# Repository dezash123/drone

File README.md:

# drone
My drone: coded in rust, frame designed in [onshape](https://cad.onshape.com/documents/91c1fbb6d04f2dc72182ab9c/w/1d5775c73044c5da3d093724/e/ebeab2adf1bd9151a745482d), and PCB designed in KiCAD.

much of this was learned through trial and error, and looking back, kinda embarrassing, but I'll keep this around since it did work

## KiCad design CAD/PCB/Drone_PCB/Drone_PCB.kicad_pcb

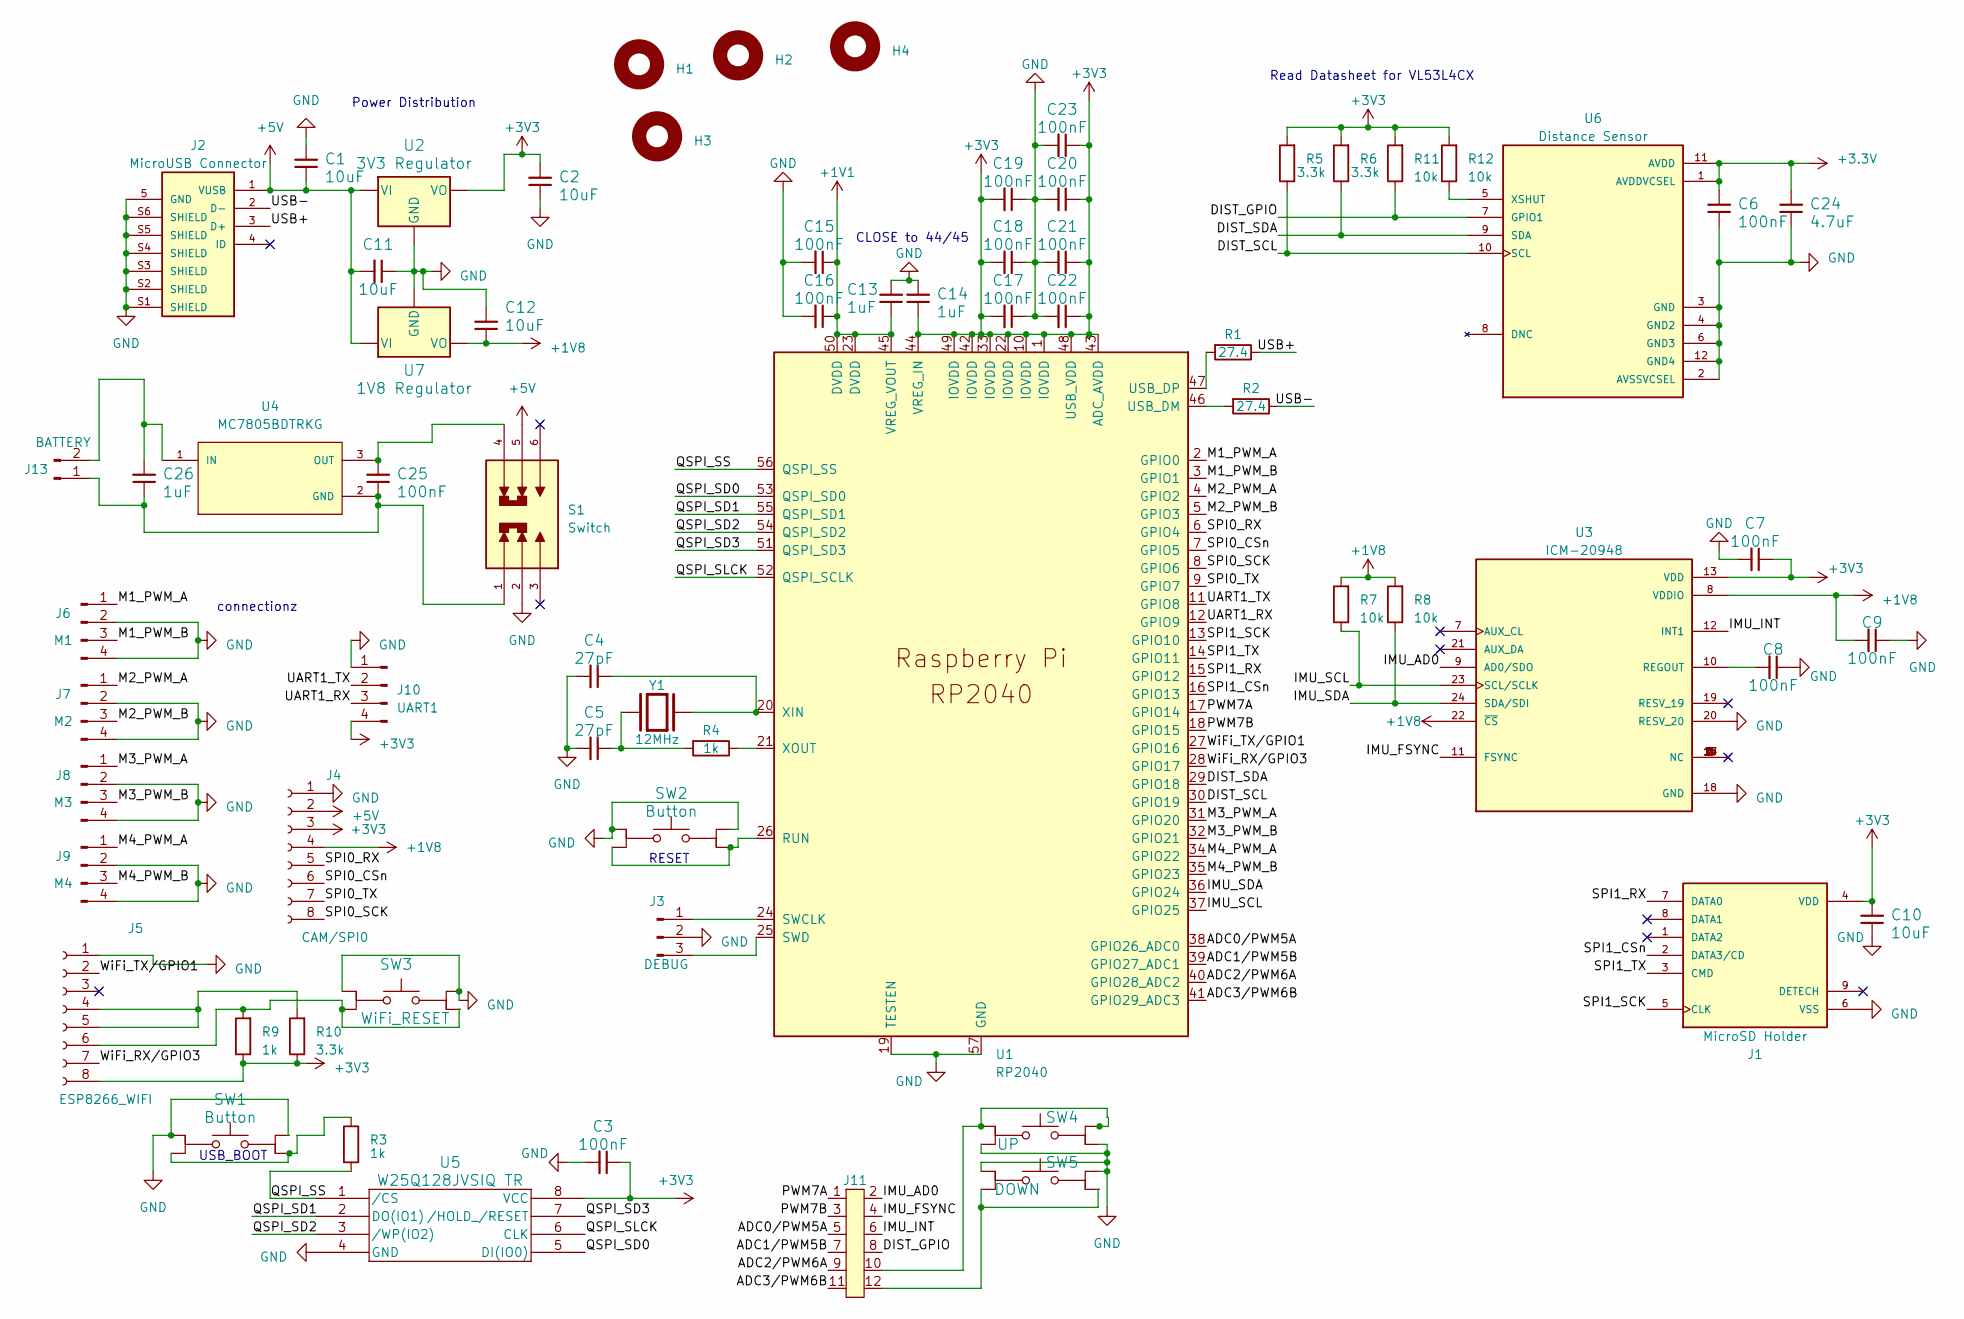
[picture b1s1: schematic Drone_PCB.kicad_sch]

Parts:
C1, C2, C10, C11, C12: 10uF; CAP_CL21_SAM
C3, C6, C7, C8, C9, C15, C16, C17, C18, C19, C20, C21, C22, C23, C25: 100nF; CAPC1005X56N
C4, C5: 27pF; CAPC1005X55N
C13, C14, C26: 1uF; CAPC1608X90N
C24: 4.7uF; CAPC1005X60N
H1, H2, H3, H4: MountingHole_2.2mm_M2
J1: MicroSD Holder; GCT_MEM2051-00-195-00-A
J2: MicroUSB Connector; AMPHENOL_10118193-0001LF; PARTREV E
J3: DEBUG; PinHeader_1x03_P2.54mm_Vertical
J4: CAM/SPI0; PinSocket_2x04_P2.54mm_Vertical
J5: ESP8266_WIFI; PinSocket_2x04_P2.54mm_Vertical
J6: M1; PinHeader_1x04_P2.54mm_Vertical
J7: M2; PinHeader_1x04_P2.54mm_Vertical
J8: M3; PinHeader_1x04_P2.54mm_Vertical
J9: M4; PinHeader_1x04_P2.54mm_Vertical
J10: UART1; PinHeader_1x04_P2.54mm_Vertical
J11: PinSocket_2x06_P2.54mm_Vertical
J13: BATTERY; AMASS_XT60-M_1x02_P7.20mm_Vertical
R1, R2: 27.4; RESC1005X35N
R3, R4, R9: 1k; RESC1005X40
R5, R6, R10: 3.3k; RESC1005X40
R7, R8, R11, R12: 10k; RESC1005X40N
S1: Switch; SW_EG2208; PARTREV C
SW1, SW2: Button; PTS 647 SN50 SMTR2 LFS
SW3: WiFi_RESET; PTS 647 SN50 SMTR2 LFS
SW4: UP; PTS 647 SN50 SMTR2 LFS
SW5: DOWN; PTS 647 SN50 SMTR2 LFS
U1: RP2040; RP2040-QFN-56
U2: 3V3 Regulator; SOT230P700X185-4N
U3: ICM-20948; QFN40P300X300X105-24N; PARTREV 1.3
U4: MC7805BDTRKG; DPAK229P990X238-4N; PARTREV 27
U5: W25Q128JVSIQ TR; SOIC_208MIL_WIN
U6: Distance Sensor; XCDR_VL53L4CXV0DH_1; PARTREV 4
U7: 1V8 Regulator; SOT223-3_ONS
Y1: 12MHz; XTAL_ABLS-12.000MHZ-K2-T; PARTREV 02.16.2021

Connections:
+1V1: C13.1, C15.1, C16.1, U1.23 (DVDD), U1.45 (VREG_VOUT), U1.50 (DVDD)
+1V8: C9.2, C12.1, J4.4, R7.2, R8.2, U3.8 (VDDIO), U3.22 (~CS), U7.2 (VO)
+5V: C1.1, C11.2, J2.1 (VUSB), J4.2, S1.5, U2.3 (VI), U7.3 (VI)
/ADC0/PWM5A: J11.5, U1.38 (GPIO26_ADC0)
/ADC1/PWM5B: J11.7, U1.39 (GPIO27_ADC1)
/ADC2/PWM6A: J11.9, U1.40 (GPIO28_ADC2)
/ADC3/PWM6B: J11.11, U1.41 (GPIO29_ADC3)
/DIST_GPIO: J11.8, R11.1, U6.7 (GPIO1)
/DIST_SCL: R5.1, U1.30 (GPIO19), U6.10 (SCL)
/DIST_SDA: R6.1, U1.29 (GPIO18), U6.9 (SDA)
/IMU_AD0: J11.2, U3.9 (AD0/SDO)
/IMU_FSYNC: J11.4, U3.11 (FSYNC)
/IMU_INT: J11.6, U3.12 (INT1)
/IMU_SCL: R7.1, U1.37 (GPIO25), U3.23 (SCL/SCLK)
/IMU_SDA: R8.1, U1.36 (GPIO24), U3.24 (SDA/SDI)
/M1_PWM_A: J6.1, U1.2 (GPIO0)
/M1_PWM_B: J6.3, U1.3 (GPIO1)
/M2_PWM_A: J7.1, U1.4 (GPIO2)
/M2_PWM_B: J7.3, U1.5 (GPIO3)
/M3_PWM_A: J8.1, U1.31 (GPIO20)
/M3_PWM_B: J8.3, U1.32 (GPIO21)
/M4_PWM_A: J9.1, U1.34 (GPIO22)
/M4_PWM_B: J9.3, U1.35 (GPIO23)
/PWM7A: J11.1, U1.17 (GPIO14)
/PWM7B: J11.3, U1.18 (GPIO15)
/QSPI_SD0: U1.53 (QSPI_SD0), U5.5 (DI(IO0))
/QSPI_SD1: U1.55 (QSPI_SD1), U5.2 (DO(IO1))
/QSPI_SD2: U1.54 (QSPI_SD2), U5.3 (/WP(IO2))
/QSPI_SD3: U1.51 (QSPI_SD3), U5.7 (/HOLD_/RESET)
/QSPI_SLCK: U1.52 (QSPI_SCLK), U5.6 (CLK)
/QSPI_SS: R3.2, U1.56 (QSPI_SS), U5.1 (/CS)
/SPI0_CSn: J4.6, U1.7 (GPIO5)
/SPI0_RX: J4.5, U1.6 (GPIO4)
/SPI0_SCK: J4.8, U1.8 (GPIO6)
/SPI0_TX: J4.7, U1.9 (GPIO7)
/SPI1_CSn: J1.2 (DATA3/CD), U1.16 (GPIO13)
/SPI1_RX: J1.7 (DATA0), U1.15 (GPIO12)
/SPI1_SCK: J1.5 (CLK), U1.13 (GPIO10)
/SPI1_TX: J1.3 (CMD), U1.14 (GPIO11)
/UART1_RX: J10.3, U1.12 (GPIO9)
/UART1_TX: J10.2, U1.11 (GPIO8)
/USB+: J2.3 (D+), R1.1
/USB-: J2.2 (D-), R2.1
/WiFi_RX/GPIO3: J5.7, U1.28 (GPIO17)
/WiFi_TX/GPIO1: J5.2, U1.27 (GPIO16)
GND: C1.2, C2.1, C3.2, C4.2, C5.2, C6.1, C7.2, C8.1, C9.1, C10.1, C11.1, C12.2, C13.2, C14.2, C15.2, C16.2, C17.1, C18.1, C19.1, C20.2, C21.2, C22.2, C23.2, C24.1, J1.6 (VSS), J2.5 (GND), J2.S1 (SHIELD), J2.S2 (SHIELD), J2.S3 (SHIELD), J2.S4 (SHIELD), J2.S5 (SHIELD), J2.S6 (SHIELD), J3.2, J4.1, J5.1, J6.2, J6.4, J7.2, J7.4, J8.2, J8.4, J9.2, J9.4, J10.1, S1.2, SW1.1, SW1.2, SW2.1, SW2.2, SW3.1, SW3.2, SW4.3, SW4.4, SW5.1, SW5.2, U1.19 (TESTEN), U1.57 (GND), U2.1 (GND), U3.18 (GND), U3.20 (RESV_20), U5.4 (GND), U6.2 (AVSSVCSEL), U6.3 (GND), U6.4 (GND2), U6.6 (GND3), U6.12 (GND4), U7.1 (GND)
unnamed: C5.1, R4.2, Y1.1
unnamed: J3.1, U1.24 (SWCLK)
unnamed: J3.3, U1.25 (SWD)
unnamed: J5.4, J5.5, R10.2
unnamed: J5.6, R9.2, SW3.3, SW3.4
unnamed: J11.10, SW4.1, SW4.2
unnamed: J11.12, SW5.3, SW5.4
unnamed: C25.1, C26.1, J13.1, S1.1, U4.2 (GND)
unnamed: C26.2, J13.2, U4.1 (IN)
unnamed: R3.1, SW1.3, SW1.4
unnamed: SW2.3, SW2.4, U1.26 (RUN)
unnamed: R2.2, U1.46 (USB_DM)
unnamed: R1.2, U1.47 (USB_DP)
unnamed: C4.1, U1.20 (XIN), Y1.2
unnamed: R4.1, U1.21 (XOUT)
unnamed: C8.2, U3.10 (REGOUT)
unnamed: C25.2, S1.4, U4.3 (OUT)
unnamed: R12.1, U6.5 (XSHUT)

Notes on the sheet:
Power Distribution
Read Datasheet for VL53L4CX
RESET
USB_BOOT
connectionz
CLOSE to 44/45

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
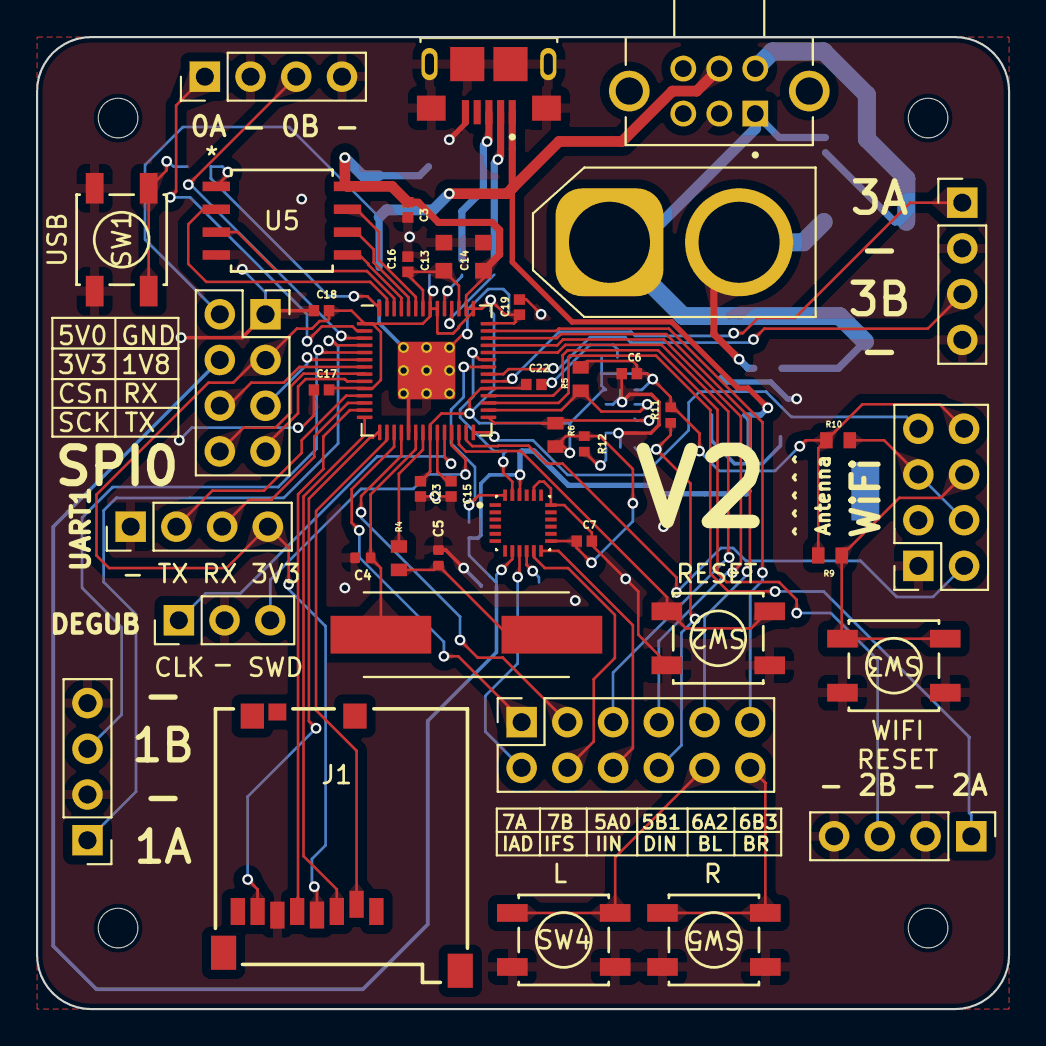
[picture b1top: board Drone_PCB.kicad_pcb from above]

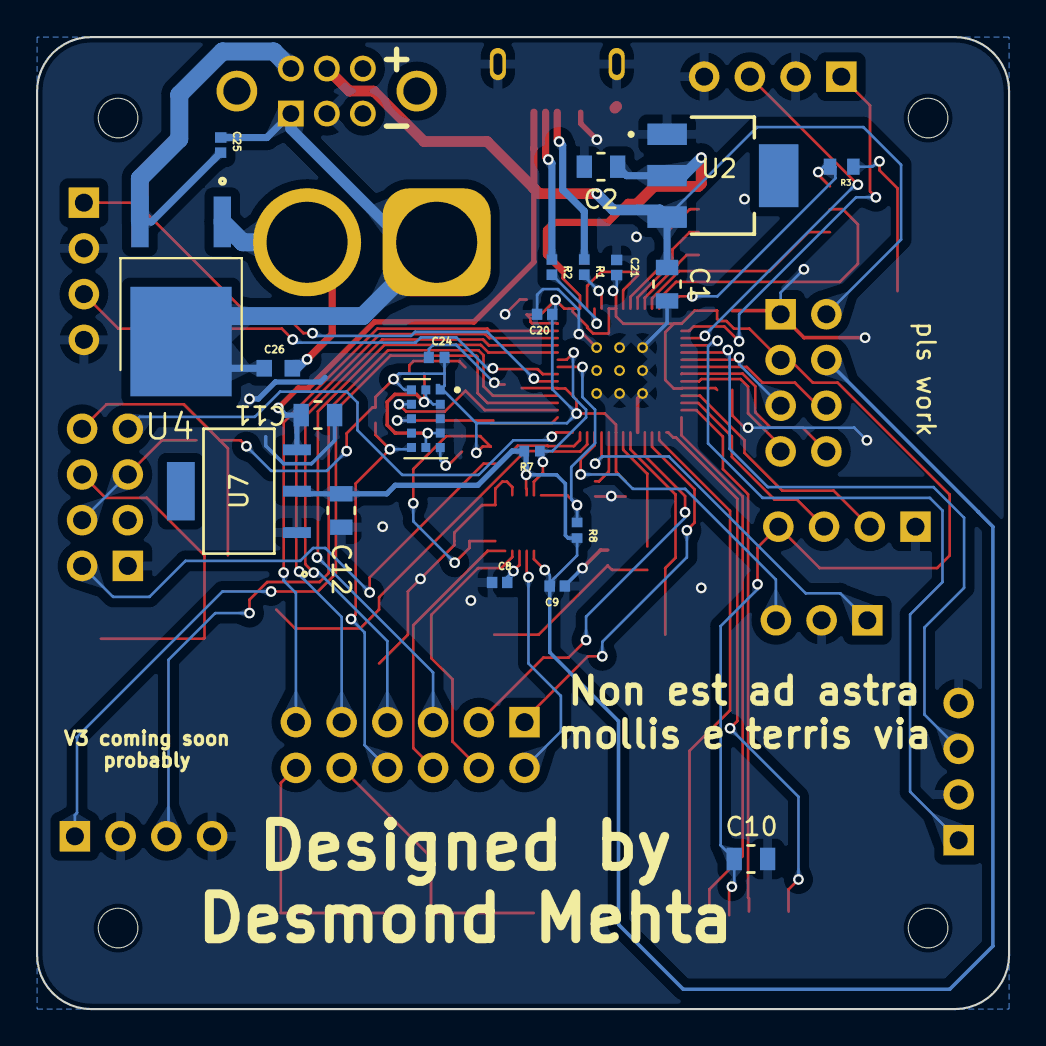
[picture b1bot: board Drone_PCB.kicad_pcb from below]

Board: 2 copper layers, 54.0 x 54.0 mm, 68 parts (21 on the bottom side), 65 nets.

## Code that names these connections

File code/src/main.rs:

#![no_std]
#![no_main]
#![feature(generic_const_exprs)]
mod control;
mod math;
mod sensors;
use crate::sensors::imu::Accelerometer;
use crate::sensors::imu::Gyroscope;
use control::radio::Radio;
use control::FlightSystem;
use core::fmt::Write;
use defmt::*;
use defmt_rtt as _;
use embedded_hal::PwmPin;
use hal::pac;
use hal::pwm::Slices;
use hal::Clock;
use panic_probe as _;
use rp2040_hal as hal;
use rp2040_hal::multicore::Multicore;
use sensors::imu::{Sensor, ICM_20948};
use crate::sensors::{AccelerometerSetting, GyroSetting};

#[link_section = ".boot2"]
#[used]
pub static BOOT2: [u8; 256] = rp2040_boot2::BOOT_LOADER_GENERIC_03H;

const EXT_CLK_HZ: u32 = 12_000_000;
const MOTOR_HZ: u32 = 1_000_000;

#[rp2040_hal::entry]
fn main() -> ! {
    let mut pac = pac::Peripherals::take().unwrap();
    let core = pac::CorePeripherals::take().unwrap();
    let mut watchdog = hal::Watchdog::new(pac.WATCHDOG);
    let mut sio = hal::Sio::new(pac.SIO);
    let slices = Slices::new(pac.PWM, &mut pac.RESETS);
    let pins = hal::gpio::Pins::new(
        pac.IO_BANK0,
        pac.PADS_BANK0,
        sio.gpio_bank0,
        &mut pac.RESETS,
    );
    let clocks = hal::clocks::init_clocks_and_plls(
        EXT_CLK_HZ,
        pac.XOSC,
        pac.CLOCKS,
        pac.PLL_SYS,
        pac.PLL_USB,
        &mut pac.RESETS,
        &mut watchdog,
    )
    .ok()
    .unwrap();
    let timer = hal::Timer::new(pac.TIMER, &mut pac.RESETS);
    let mut delay = cortex_m::delay::Delay::new(core.SYST, clocks.system_clock.freq().to_Hz());
    let mut imu = ICM_20948::new(
        AccelerometerSetting::r4g,
        GyroSetting::r250dps,
        pac.I2C0,
        pins.gpio24.into_mode(),
        pins.gpio25.into_mode(),
        &mut pac.RESETS,
    );
    let mut radio = Radio::new(
        pac.UART1,
        pins.gpio4.into_mode(),
        pins.gpio5.into_mode(),
        &mut pac.RESETS,
        clocks.peripheral_clock.freq(),
    );
    let mut p0 = slices.pwm0;
    let mut p1 = slices.pwm1;
    let mut p2 = slices.pwm2;
    let mut p3 = slices.pwm3;
    // standard 1-2 ms pwm
    let pwm_int: u8 = 4;
    let pwm_frac: u8 = 12;

    // multishot
    // let pwm_int: u8 = 0;
    // let pwm_frac: u8 = 1;

    p0.set_div_int(pwm_int);
    p1.set_div_int(pwm_int);
    p2.set_div_int(pwm_int);
    p3.set_div_int(pwm_int);
    p0.set_div_frac(pwm_frac);
    p1.set_div_frac(pwm_frac);
    p2.set_div_frac(pwm_frac);
    p3.set_div_frac(pwm_frac);
    p0.enable();
    p1.enable();
    p2.enable();
    p3.enable();
    let mut m0 = p0.channel_a;
    let mut m1 = p1.channel_a;
    let mut m2 = p2.channel_a;
    let mut m3 = p3.channel_a;
    let _ = m0.output_to(pins.gpio0);
    let _ = m1.output_to(pins.gpio2);
    let _ = m2.output_to(pins.gpio20);
    let _ = m3.output_to(pins.gpio22);
    let mut mc = Multicore::new(&mut pac.PSM, &mut pac.PPB, &mut sio.fifo);
    let cores = mc.cores();
    let core1 = &mut cores[1];
    let mut flight_system = FlightSystem::new(m0, m1, m2, m3, timer);
    flight_system.start(delay, imu, radio, core1);
}

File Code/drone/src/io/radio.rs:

// FlySky iA6B ibus interface
// only rx for now
use cortex_m::delay::Delay;
use cortex_m::prelude::_embedded_hal_serial_Read;
use defmt::info;
use defmt::Format;
use fugit::HertzU32;
use fugit::RateExtU32;
use hal::gpio::bank0::{Gpio0, Gpio1, Gpio16, Gpio17};
use hal::gpio::Function;
use hal::gpio::Pin;
use hal::i2c::I2C;
use hal::uart::ValidUartPinout;
use hal::{
    clocks::init_clocks_and_plls,
    gpio::{FunctionUart, Pins},
    pac::{self, UART0},
    sio::Sio,
    uart::{
        self, DataBits, Parity, ReadError, ReadErrorType, Reader, StopBits, UartConfig,
        UartPeripheral,
    },
    watchdog::Watchdog,
    Clock,
};
use nb::Error;
use nb::Error::Other;
use rp2040_hal as hal;

pub enum RadioError {
    ChecksumError,
    ReadError(Option<hal::uart::ReadErrorType>),
}

pub struct Radio {
    reader: Reader<
        pac::UART0,
        (
            Pin<Gpio0, Function<hal::gpio::Uart>>,
            Pin<Gpio1, Function<hal::gpio::Uart>>,
        ),
    >,
    pub buf: [u8; 31],
}

impl Radio {
    pub fn new(
        uart0: pac::UART0,
        miso: Pin<Gpio0, Function<hal::gpio::Uart>>,
        mosi: Pin<Gpio1, Function<hal::gpio::Uart>>,
        resets: &mut pac::RESETS,
        peripheral_clock_freq: fugit::HertzU32,
    ) -> Self {
        let mut uart = UartPeripheral::new(uart0, (miso, mosi), resets)
            .enable(
                UartConfig::new(115200.Hz(), DataBits::Eight, None, StopBits::One),
                peripheral_clock_freq,
            )
            .unwrap();
        uart.set_fifos(true);
        Self {
            reader: uart.split().0,
            buf: [0; 31],
        }
    }
    pub fn read(&mut self) -> Result<(), RadioError> {
        let mut newdata: [u8; 31] = [0; 31];
        let first = match nb::block!(self.reader.read()) {
            Ok(n) => n,
            Err(e) => {
                return Err(RadioError::ReadError(Some(e)));
            }
        };
        if first != 0x20 {
            return Err(RadioError::ReadError(None));
        }
        match self.reader.read_full_blocking(&mut newdata) {
            Ok(()) => (),
            Err(e) => return Err(RadioError::ReadError(Some(e))),
        };
        let mut checksum: u16 = 0xffdf;
        for i in &newdata[0..29] {
            checksum -= *i as u16;
        }
        if checksum != u16::from_be_bytes([newdata[30], newdata[29]]) {
            return Err(RadioError::ChecksumError);
        }
        self.buf = newdata;
        return Ok(());
    }
    pub fn get_command(&self) -> RadioCommand {
        let mut channels: [f32; 6] = [0.0; 6];
        for i in 1..7 {
            let cval = u16::from_be_bytes([self.buf[i * 2], self.buf[i * 2 - 1]]);

            channels[i - 1] = if cval < 1000 {
                0.0
            } else if cval > 2000 {
                1.0
            } else {
                (cval - 1000) as f32 / 1000.0
            };
        }
        RadioCommand {
            z_throttle: channels[2],
            y_throttle: channels[1] * 2.0 - 1.0,
            x_throttle: channels[0] * 2.0 - 1.0,
            twist_throttle: channels[3] * 2.0 - 1.0,
            mode_select: channels[4],
            total_throttle: channels[5],
        }
    }
}

#[derive(Debug, Format, Clone, Copy)]
pub struct RadioCommand {
    z_throttle: f32,
    y_throttle: f32,
    x_throttle: f32,
    twist_throttle: f32,
    mode_select: f32,
    total_throttle: f32,
}

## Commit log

2023-04-25 organization
2023-05-12 PCB CAD git add .git add .
2023-05-13 stuff
2023-05-20 doin stuff
2023-05-22 finished pcb
2023-05-24 pcb actually done
2023-06-06 rust??
2023-06-11 not much
2023-06-11 rust!!
2023-06-16 pcb V2
2023-06-17 finished PCB V2
2023-06-19 more rust
2023-06-19 cleaning
2023-06-23 more
2023-07-08 wrote most of IMU driver
2023-07-08 wrote most of IMU drive
2023-07-09 saving nice errors but might have to remove
2023-07-14 NO VECTORS
2023-07-14 maybe change to MPU; traitsgit add .
2023-07-27 many stuff
2023-07-27 NO MORE DRIVERS
2023-07-28 asdgrew4hestndg
2023-07-29 reorganized and removed unnecessary STEP files
2023-07-29 more cleanup
2023-07-29 gitignore
2023-09-09 pidslsls
2023-09-09 twist
2023-09-09 order makes sense now
2023-09-09 ok now its organized
2023-09-15 liftoffgit add .
2023-09-19 MPC Kalman filters AAAA
2023-09-22 MPC?
2023-09-22 asdf
2023-09-25 aaaaaaaaaaaaaaaaaaaaaaaaaaaaa
2023-11-09 no more pids
2023-11-09 redoing imu for millionth time and adding magnetometer readings for absolute angle
2023-11-13 things and stuff
2024-04-01 idk some stuff
